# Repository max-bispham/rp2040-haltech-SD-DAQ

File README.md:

# FSAE Backup CAN Logger

**Status:** Hardware architecture selected; firmware and breadboard validation not yet complete.  
**Updated:** October 21, 2026  
**Target:** A practical demonstration for the FSAE electrical-team freshmen on October 22, 2026, at 8 PM.

> **Purpose:** A low-cost, independent backup system that passively captures the car's Haltech CAN traffic onto microSD and presents recorded runs as ordinary files on Windows, macOS, and Linux. This is a data-collection accessory, **not** a replacement for the ECU/PDM, safety systems, or the main DAQ.

## 1. The design in one minute

- **Microcontroller:** Existing Raspberry Pi **Pico / RP2040**; no replacement development board.
- **CAN interface:** **Waveshare Pico-CAN-B** (SKU 23775) with MCP2515, SIT65HVD230DR, 16 MHz crystal, 3.3 V logic. This replaces the user's existing **8 MHz MCP2515/TJA1050** breakout, which cannot be set to compliant 1 Mbit/s CAN timing.
- **Storage:** Existing SPI microSD breakout, on a separate RP2040 SPI peripheral; breakout model/electrical requirements **still need verification**.
- **Computer connection:** Pico's built-in USB device controller running **USB Mass Storage Class (MSC)**, backed by the microSD card. A computer uses its normal file manager: no serial commands, Python, Wi-Fi, or custom host driver for **retrieving** recordings.
- **USB socket:** Use the Pico's existing **Micro-USB socket on the bench**. For the finished carrier PCB, investigate wiring the already-owned **Adafruit #4090 USB-C breakout** to the Pico's underside USB test pads with short matched traces. Do not connect two simultaneous host cables.
- **Controls:** Button; green power-good indicator; dim/bright red recording indicator; yellow USB-presence indicator.
- **Vehicle power:** A **regulated 5 V supply** fed from a suitable, configured and protected PD16 **battery-voltage** output, **not** the PD16 5 V sensor reference. The final converter and source-selection/backfeed protection circuit are not yet fixed.
- **System software:** C++ using Arduino-Pico, a proven microSD library, TinyUSB MSC, and an MCP2515 driver. **No FreeRTOS required for the first milestone.** PC-side Python handles *optional* decoding/graphing after users have already copied data from the USB drive.
- **Mechanical:** Eventual 2-layer KiCad carrier PCB for the existing modules and a 3D-printed enclosure. An editable **Fritzing wiring sketch is a separate upcoming artifact**. This README does not claim that the wiring is physically verified yet.

### What we already have versus what is new

| Part | Source | Notes |
|---|---|---|
| Raspberry Pi Pico/RP2040 board | Already owned | Assumes a **standard 40-pin Pico pinout**; check variant |
| SPI microSD breakout and microSD card | Already owned | Confirm VCC requirements and module labeling |
| Adafruit 4090 USB-C connector breakout | Already owned | Future enclosure connector, not an SD reader |
| Pushbutton and green/red/yellow LEDs | Already owned | Resistors required |
| **Waveshare Pico-CAN-B** | One replacement module | Needed for 1 Mbit/s and direct 3.3 V interfacing |
| 12 V/battery to 5 V buck converter | Planned order | Only necessary for powered operation in the vehicle |
| Typical resistors/capacitors and connectors | Bench stock | See electrical notes |

**Do not purchase another RP2040, a USB-storage shield, an ESP32, a logic-level translator, or a separate CAN transceiver for this design.** The Waveshare module includes both controller and transceiver and is specified for 3.3 V operation.

## 2. User-facing behavior

1. When vehicle power is applied, the device initializes its CAN receiver and SD card.
2. **Red dim solid** means the logger is ready. Press the button to create a new run.
3. **Red bright, blinking once per second** means recording is active. Every received frame is timestamped and stored, including frames whose meaning is not yet known.
4. Press the button again to stop. The red LED goes **off** while buffers are drained and the FAT filesystem is flushed/closed; once complete the red LED returns to dim solid.
5. Connect a computer over USB. Recording stops/is disabled, the microSD is exclusively handed to the USB mass-storage device, and the computer sees a disk (recommended FAT32 volume label `FSAE_LOGGER`). Users can drag files into a folder without special software.
6. Safely eject the disk before unplugging. After USB disconnect, the logger may return to ready mode once the microSD is reinitialized.
7. Optional: a Python analysis script on an engineering laptop picks the most recent run, decodes the known Haltech channels, and generates graphs. **Python must never be required merely to retrieve log files.**

### LED definitions

| LED | Meaning | Recommended implementation |
|---|---|---|
| Green | Regulated supply in acceptable operating range | GPIO output based on a divider/ADC measurement of the 5 V system rail; do not equate an LED connected to power with precision voltage supervision |
| Red dim solid | SD + logging subsystem initialized, ready | RP2040 PWM low duty cycle |
| Red bright blink at 1 Hz | Recording | RP2040 PWM high duty cycle, 1-second blink period |
| Red off | Booting, finalizing, USB MSC or fault | State machine |
| Yellow on | USB host power (VBUS) is present | Pico's onboard USB VBUS-sense path (GPIO24 on a **standard Pico**) drives separate GPIO LED; host enumeration is a different status |

**Fail-safe behavior:** Never indicate 'recording' when the SD card is missing, full, unmounted, or has failed writes. Log faults/counters in a sidecar when possible.

## 3. Electrical interfaces and proposed GPIO map

**These are proposed electrical assignments, not a finished PCB netlist.** Cross-check the actual Pico variant, SD module pin labels, Waveshare board revision, and the physical board stacking clearance before wiring.

### CAN: Waveshare Pico-CAN-B (manufacturer schematic)

The board contains an MCP2515 with a **16 MHz oscillator** and an **SN65HVD230-family 3.3 V CAN transceiver** (Waveshare product description names it SIT65HVD230DR). The schematic connects:

| CAN signal | RP2040 GPIO | Pico physical pin | Function |
|---|---:|---:|---|
| SPI0 MISO (MCP2515 SO) | GP4 | 6 | Controller -> Pico |
| SPI0 CS0 | GP5 | 7 | Chip select |
| SPI0 SCK | GP6 | 9 | Clock |
| SPI0 MOSI (MCP2515 SI) | GP7 | 10 | Pico -> controller |
| MCP2515 INT | GP21 | 27 | Receive/event interrupt (default 0-ohm option) |
| CAN H | Module terminal | — | CAN high |
| CAN L | Module terminal | — | CAN low |
| CAN ground | Module terminal | — | Reference / harness ground, verify terminal orientation |

**Conflict resolved:** The previous draft used **GP5 for a green/red indicator**; that GPIO now belongs to the CAN module. **Do not use GP5 as an LED.** No additional SPI-level converter is needed with this specified Waveshare module.

**Bus configuration:** Classic CAN, 1,000,000 bit/s, standard 11-bit identifiers. Configure the MCP2515 for its **actual 16 MHz oscillator** and **listen-only receive**; the logger must not transmit commands, acknowledgments or error frames onto the running vehicle's bus. Other active nodes supply any needed ACKs. Verify behavior on an isolated test bus before connecting to the car.

**Termination:** The Waveshare board has a selectable **120 Ω** termination. The existing bus should have **two 120 Ω terminations at its physical endpoints**. If the logger is a short additional stub on an already terminated bus, leave the module's termination **off**. Do not casually add a third termination resistor.

**Important receive limitation:** MCP2515 provides only two hardware receive buffers; SD write stalls can therefore cause real CAN losses even with a RAM queue. Count MCP2515 RX overflow and firmware queue overflow separately, make draining CAN a priority, and load-test under representative bus traffic.

### microSD: separate RP2040 SPI1 peripheral

| SD signal (confirm module silkscreen) | RP2040 GPIO | Pico physical pin |
|---|---:|---:|
| DO / MISO | GP12 | 16 |
| CS / SS | GP13 | 17 |
| CLK / SCK | GP14 | 19 |
| DI / MOSI | GP15 | 20 |
| VCC | 3V3(OUT) **only if the module is 3.3 V compatible** | 36 |
| GND | GND | Any suitable GND pin |

**Breakout specification is still unknown.** Some SD breakout boards expect a **5 V input** because they carry an onboard regulator/level shifting; some expect only **3.3 V**. Confirm the actual board before applying power. Native microSD cards are 3.3 V devices. Put **100 nF ceramic + around 10 µF bulk capacitance** near the module supply, subject to what the module already provides. All grounds must share a valid common reference.

### Controls and indicators (nonconflicting GPIOs)

| Function | RP2040 GPIO | Pico physical pin | Connection |
|---|---:|---:|---|
| Record button | GP2 | 4 | Normally-open switch to GND; internal pull-up; debounce in firmware |
| Red recording LED | GP3 | 5 | GPIO -> 330-1k Ω resistor -> LED -> GND; PWM brightness |
| Green power LED | GP8 | 11 | GPIO -> 330-1k Ω resistor -> LED -> GND |
| Yellow USB LED | GP9 | 12 | GPIO -> 330-1k Ω resistor -> LED -> GND |
| Regulated 5 V rail monitor | GP26 / ADC0 | 31 | Through a voltage divider only; **never feed 5 V directly to a GPIO** |
| Native USB VBUS sense | GP24 (internal Pico wiring) | Not header-accessible | Reads presence of USB VBUS on standard Pico |

**Example voltage divider:** 100 kΩ from regulated 5 V rail to GP26, 100 kΩ from GP26 to ground. At a 5.5 V maximum rail, ADC input is about 2.75 V. Select and calibrate a threshold in firmware; green LED only means the monitored rail passes the defined threshold, not that the power supply is automotive-certified. Confirm ADC reading stability in USB-only operation. Keep LED forward current within Pico GPIO constraints; 330-1k Ω series resistance is appropriate for preliminary testing.

### USB mass storage and the eventual USB-C interface

- **Bench:** Use the Pico's own **Micro-USB** receptacle. The RP2040 already has native USB device hardware; no USB bridge module is required.
- **Storage firmware:** Use Adafruit TinyUSB MSC on Arduino-Pico. A supported SD-card MSC example exists, but it must be adapted to the specific SPI bus and to exclusive SD ownership.
- **Carrier PCB concept:** The standard Pico exposes USB **D- on TP2** and **D+ on TP3** underneath the board; **TP1 is USB-adjacent ground**. The Adafruit #4090 exposes USB-C D-/D+/VBUS/GND and incorporates CC resistors. A two-layer carrier can route the short D+/D- pair over continuous ground with appropriate differential geometry; exact impedance is layout-dependent. Accessing Pico underside pads will require a sound manufacturing/contact method; standard headers alone do not connect the test pads.
- **USB-C caveat:** Connecting a separate USB-C socket to TP2/TP3 leaves the Pico's own Micro-USB receptacle electrically on the same USB interface. **Only one cable/host may be used at a time.** Review stubs, ESD protection, power routing and mechanical reliability before fabrication.
- **Power caveat:** The USB VBUS conductor must not be hard-shorted to a powered vehicle 5 V buck output. Plan proper power-source selection/backfeed blocking. This is deliberately not finalized in the breadboard sketch.
- **Filesystem ownership:** Never have MCU FAT writes active while USB MSC is exporting raw SD sectors. On USB insertion, end the run, flush, close, synchronize the writer, and only then make MSC ready. In MSC mode, the internal logger is locked out. Start with read-only MSC if reliable host read-only behavior is acceptable; test on all three operating systems.
- **Volume label:** Set FAT32 volume label to `FSAE_LOGGER` when formatting the card; the USB product string does not itself set the filesystem volume label.

### Vehicle power (still to be finalized)

The PD16 has a dedicated **5 V sensor supply limited to 200 mA total** (PD16 wiring diagram, Connector A pin 12). This is **not** recommended for the logger; its headroom is shared with other sensors. Configurable high-current PD16 outputs provide **switched battery voltage**, not an adjustable regulated 5 V output. **PWM averaging is not a safe substitute for a buck regulator.**

The proposed final route is: appropriately programmed/fused PD16 high-side battery output -> suitable 12 V-to-5 V buck converter -> protected, backfeed-safe 5 V logger supply -> Pico VSYS and any compatible peripherals. Keep USB power availability for file retrieval with the vehicle switched off. Test supply behavior during startup/shutdown and SD writes; an ordinary low-cost buck should not automatically be treated as a fully transient-qualified automotive design.

**For today, use the Pico's normal USB power. No buck converter is required for simulated data/SD/MSC development at the desk.**

## 4. Firmware architecture (proposed; code not started)

```text
Waveshare CAN H/L -> 16 MHz MCP2515/SIT65HVD230 -> SPI0 + GP21 interrupt
                                                    |
                                         Receive + timestamp raw frame
                                                    |
                                               RAM ring buffer
                                                    |
                                       batched, sequential SD writer
                                                    |
                           SPI1 -> microSD FAT32 -> RUN00001.BIN, etc.
                                                    |
                      exclusive ownership handoff (recording stopped)
                                                    |
                     Native RP2040 USB device -> USB MSC -> host file manager
```

Design principles:

1. **Log raw CAN frames first; decode later.** This preserves Elite ECU, PD16, wideband and other traffic even when interpretation is incomplete.
2. Start with a simple nonblocking single-core implementation for generated traffic and SD/USB bring-up. Once hardware CAN is connected, test whether SD stalls cause MCP2515 hardware overrun. If necessary, use RP2040's two cores with a synchronized queue and separate SPI peripherals: one core continuously services CAN; the other writes SD. Two SPI interfaces **alone** do not make CPU operations concurrent.
3. Avoid FreeRTOS for v1. It is an option only if measurable timing/ownership requirements justify it.
4. Allocate fixed-size buffers; prohibit indefinite blocking in the receive path. Record dropped-frame/overflow/write-error counters rather than silently misrepresenting missing data.
5. Have exactly one owner of the SD controller/filesystem at a time: recorder **or** USB host mass storage.
6. USB storage and recording are **mutually exclusive**. USB attachment during recording should stop and finalize first, then enumerate or report unit-not-ready until the card is released.
7. Storage is a **best-effort backup** without a guaranteed power-fail hold-up. Periodically flush and validate how logs behave under unexpected removal of power.

### Logical states

```text
BOOT -> READY -> RECORDING -> FINALIZING -> READY
            \                         /
             \--- USB insertion -----/ -> USB_MSC -> (USB disconnect) -> READY
Any state --(unrecoverable fault)--> ERROR
```

USB MSC must never advertise the card as ready while the MCU still has open log files. A USB cable connected to a USB-powered logger is not the same as a connected host successfully mounting a filesystem: separate those diagnostics when testing.

## 5. Log file format (design proposal; freeze before code generation)

Use FAT32 and incrementing session filenames such as `RUN00001.BIN` plus a human-readable `RUN00001.JSON` summary on a **clean stop**. No real-time clock is assumed; filename/session index, not creation date, defines the latest run.

The format below is a proposal from the first planning draft, retained for continuity. It is **not** a Haltech proprietary format and not yet implemented.

**32-byte header** (all container integers little-endian):

| Offset | Bytes | Field |
|---:|---:|---|
| 0 | 8 | ASCII `FSAECAN1` |
| 8 | 2 | Format version = 1 (`uint16`) |
| 10 | 2 | Header size = 32 (`uint16`) |
| 12 | 2 | Record size = 24 (`uint16`) |
| 14 | 2 | Flags = 0 (`uint16`) |
| 16 | 4 | Timebase ticks per second = 1,000,000 (`uint32`) |
| 20 | 4 | Session number (`uint32`) |
| 24 | 8 | Reserved zeros |

**24-byte frame record** (`struct` format `<QHBB8sI`):

| Offset | Bytes | Field |
|---:|---:|---|
| 0 | 8 | Microseconds since start of run (`uint64`) |
| 8 | 2 | Standard CAN ID (`uint16`, 0–0x7FF) |
| 10 | 1 | DLC (`uint8`, 0–8) |
| 11 | 1 | Flags; zero for ordinary standard CAN data frame |
| 12 | 8 | Raw CAN payload bytes, zero-padded only beyond DLC |
| 20 | 4 | Monotonic sequence number (`uint32`) |

**Important:** Haltech's **payload bytes remain unchanged**. The binary container's little-endian integers and Haltech's big-endian *signal interpretation* are separate concepts. Include a clean-stop JSON with frame counts, queue drops, MCP2515 overflow counts, SD write errors, bitrate/oscillator, session number, and whether finalization succeeded. Be tolerant of truncation or missing JSON after sudden loss of power.

Example bandwidth: 5,000 recorded frames/s × 24 bytes = **120,000 bytes/s** not counting filesystem overhead. Size the RAM queue according to measurement, not that one example alone.

## 6. CAN protocol notes from the attached Haltech PDFs

**ECU Broadcast CAN Protocol v2.0:** 1 Mbit/s; standard 11-bit IDs; big-endian multibyte fields; listed ECU Elite firmware **3.11+** for full support. Available broadcast channels depend on the ECU firmware and actual NSP setup. A CAN logger cannot access arbitrary internal ECU logger channels that are not transmitted on the bus.

| ECU ID | Documented rate | Sample decoding targets |
|---|---:|---|
| `0x360` | 50 Hz | Bytes 0–1 RPM (`u16be`); 2–3 manifold pressure kPa absolute (`u16be / 10`); 4–5 throttle % (`u16be / 10`) |
| `0x361` | 50 Hz | 0–1 fuel pressure kPa gauge (`u16be/10 - 101.3`); 2–3 oil pressure gauge (same) |
| `0x362` | 50 Hz | 0–1 and 2–3 injector duty cycles; 4–5 ignition angle (`s16be/10`) |
| `0x368` | 20 Hz | Four wideband lambda values: consecutive 16-bit unsigned words divided by 1,000 |
| `0x36C` | 20 Hz | Four wheel speeds in km/h: four unsigned 16-bit words divided by 10 |
| `0x372` | 10 Hz | 0–1 battery voltage V (`u16be/10`) |
| `0x3E0` | 5 Hz | Four temperatures: each `u16be/10` Kelvin, then subtract 273.15 for Celsius |

**PD16 Multiplexed CAN Protocol v2.0 (newly supplied PDF):** Also uses 1 Mbit/s, 11-bit IDs, and big-endian values. PD16 base CAN identifiers: **A `0x6D0`, B `0x6D8`, C `0x6E0`, D `0x6E8`**. The first payload byte of a multiplexed message selects IO type/index; **do not** interpret every message sharing a CAN ID as the same channel without using that multiplex field. The document separately defines **PD16-to-ECU** broadcast IDs for monitored input states (PD16 A includes `0x320`, `0x324`, `0x328` at listed 100 Hz rates). Device commands and reported state data are different directions. Read the protocol tables before building a full decoder.

See PDF source files at project root or team repository `docs/` folder, as available:

- `Broadcast_CAN_Protocol_Document_Version_2.pdf` — ECU protocol, pp. 2–7 and subsequent channel tables.
- `Multiplexed_CAN_Protocol_Document_Version_2.pdf` — PD16 support/IDs, pp. 3, 5, 13–17 and later tables.
- `haltech-can-protocol-specification.pdf` — supplementary bit addressing, units and conventions.

The ECU's `0x368` values are **ECU-broadcast wideband channels**; an independent wideband module may use another protocol. Record every ID and determine what really appears on the car before promising channel coverage.

## 7. Desktop analysis expectations

The **USB drive** is the nontechnical user's default interface. Its raw run files must be accessible without Python. A separate, engineering-oriented Python program may:

1. Select the numerically highest valid `RUNxxxxx.BIN`, or accept a specific file path.
2. Validate header, DLCs, record length, monotonic time/sequence, and truncated tail data.
3. Decode known Elite/PD16 channels with proper byte order, signedness, rates and scaling; retain unknown frames.
4. Plot selected channels against **run-relative time** (RPM, throttle, MAP, fuel/oil pressure, coolant temperature, voltage, lambda, PD16 power-channel data where documented/observed).
5. Export selected channels as CSV for Excel or other tools; a double-clickable desktop front end can come later, but is not needed merely to copy logs.

## 8. Recommended development stages

| Milestone | What to demonstrate | Requires new CAN module? |
|---|---|---|
| 1. SD smoke test | Initialize card; write/read a test file | No |
| 2. Simulated run capture | Generate plausible test CAN frames, record on button press and stop reliably | No |
| 3. Native USB mass storage | Mount card in Windows/Linux/macOS file manager via Pico Micro-USB; safely copy files | No |
| 4. Indicators and ownership | LED states; no simultaneous host/MCU card access; repeated start/stop/eject cycles | No |
| 5. PC decoder/plots | Convert simulated log to sensible graphs / CSV | No |
| 6. Receive CAN traffic | Initialize Waveshare MCP2515 at 16 MHz/1 Mbps, listen-only, count overflows | **Yes** |
| 7. Stress test | CAN bursts while SD writes, verify no silent losses | **Yes** |
| 8. Car integration | Check vehicle CAN termination/bus configuration and safely compare data with NSP | **Yes** |
| 9. Carrier and enclosure | Fritzing wiring sketch, KiCad PCB, USB-C routing, final power circuit | Physical measurements and review |

**Meeting goal:** Demonstrate steps 1–5 if time permits, with generated data; clearly label simulated traffic so it is not confused with live car data. A functioning, honestly limited prototype is better than an unverified complete system.

### Draft repository layout

```text
fsae-can-logger/
├── README.md
├── firmware/
│   ├── include/           # config/pin map; logging record definition
│   └── src/               # app, state machine, CAN, SD, USB MSC, LEDs
├── tools/
│   └── plot_latest.py     # engineering-side decoder and plots (planned)
├── tests/
│   └── ...                # fake frames, binary parser tests (planned)
├── hardware/
│   ├── fritzing/          # future editable .fzz sketch
│   └── kicad/             # future carrier board
└── docs/
    └── ...                # optional copies of Haltech PDFs
```

## 9. Outstanding questions (before fabrication, not blockers for milestone 1)

- Exact model/photo of microSD breakout; verify whether its **VCC** is 3.3 V or 5 V, presence of level shifting and on-board capacitors.
- Exact variant of the Pico and access to its pins while Pico-CAN-B is stacked.
- Whether Waveshare module arrives as ordered; verify its crystal and physical jumper position. Confirm **MCP2515 INT on GP21** and controller CS on GP5 on the delivered board.
- Existing CAN physical-end termination, tap length, and Elite CAN broadcast configuration.
- Selected PD16 high-side power pin, programmed fuse/enable behavior, regulated 5 V converter, and USB/vehicle power source-selection protection.
- Mechanical arrangement and tolerances of the Pico, CAN module, SD breakout and USB-C breakout, including Pico underside USB test-pad contact plan.
- Whether the initial USB drive will be **read-only** or writable by the host; in either case enforce exclusive SD ownership.
- Whether USB should stop an ongoing run automatically or require the operator to press Stop first. Default recommendation: automatic safe finalization when feasible, never immediate raw mounting during active recording.

## 10. Updated and spelling-corrected project brief

> I have an opportunity to develop a backup data logger for our FSAE team's car. Our primary data acquisition system may not be fully reliable or ready for testing, so I want an independent system that collects data already transmitted on the car's CAN network. I want a concrete proposal and ideally a small demonstration for our freshmen team members tomorrow at 8 PM.
>
> The car uses a Haltech Elite 1500 ECU, a Haltech Nexus PD16 power distribution module, and a Haltech CAN-connected oxygen sensor. Much of the information we want is already on the CAN bus. The backup device should capture complete raw CAN frames to a microSD card and allow us to decode and graph selected measurements after a run.
>
> The most important usability requirement is that any team member, including mechanical engineers who do not know Python or command-line tools, can plug the device into a Windows, macOS, or Linux laptop and see the recorded files in the operating system's file manager. Wi-Fi is not suitable as the primary retrieval method because the laptop may not be near the car after a run, and connecting the car to the university network is inconvenient.
>
> Hardware requirements: a CAN reader compatible with Haltech's 1 Mbit/s, 11-bit classic CAN network; an SPI microSD card interface; native USB mass storage, eventually through our Adafruit #4090 USB-C connector breakout; a green adequate-power LED; a red status LED that is faint and steady in standby, bright and blinking once per second during recording, and off while processing or not ready; a yellow USB-connected LED; and a pushbutton to start/stop recording. The unit should eventually be powered by a protected, regulated 5 V source from the PD16 system.
>
> We chose our existing RP2040/Pico because it is inexpensive, has native USB device support and enough capacity for a small CAN-to-SD logger. Our current MCP2515/TJA1050 module has an 8 MHz crystal and is not a good match for 1 Mbit/s operation, so we are replacing **only that CAN module** with a Waveshare Pico-CAN-B, which includes a 16 MHz MCP2515 and 3.3 V CAN transceiver. We will reuse our existing microSD breakout, LEDs, pushbutton and USB-C breakout. We do not need FreeRTOS unless later measurements demonstrate a need.
>
> Eventually the components will mount to a two-layer KiCad carrier PCB manufactured at school, inside a 3D-printed enclosure. We may use Fritzing for a clear editable breadboard wiring diagram. The design does not have to be waterproof but must be electrically safe for a passive, receive-only connection to the car and able to produce useful, retrievable logs.
>
> Please help validate the hardware, architecture and pinout; identify specification mismatches; document the system and protocols; plan realistic development phases; and prepare reviewed, modular prompts for Claude to implement the firmware and Python analysis tools. Do not begin generating code until we approve the design and set up the development environment and breadboard.

## 11. Verified reference links

- [Waveshare Pico-CAN-B product page (SKU 23775)](https://www.waveshare.com/product/pico-can-b.htm)
- [Waveshare Pico-CAN-B schematic (Pico pin map, controller/transceiver, 16 MHz clock)](https://files.waveshare.com/upload/1/13/PICO-CAN-B-sch.pdf)
- [Waveshare Pico-CAN-B documentation](https://www.waveshare.com/wiki/Pico-CAN-B)
- [Raspberry Pi Pico datasheet (pinout, USB TP1/TP2/TP3, supply constraints)](https://datasheets.raspberrypi.com/pico/pico-datasheet.pdf)
- [Adafruit USB-C breakout #4090](https://www.adafruit.com/product/4090)
- [Arduino-Pico USB / Adafruit TinyUSB documentation](https://arduino-pico.readthedocs.io/en/latest/usb.html)
- [Adafruit TinyUSB SD-card USB MSC example](https://github.com/adafruit/Adafruit_TinyUSB_Arduino/blob/master/examples/MassStorage/msc_sd/msc_sd.ino)
- [Haltech PD16 wiring diagram (5 V sensor supply: 200 mA maximum)](https://www.jbtechracing.com/wp-content/uploads/2023/10/PD16_WiringDiagram-1.pdf)
- [Haltech Elite/ECU broadcast CAN reference](https://support.haltech.com/portal/en/kb/articles/haltech-can-ecu-broadcast-protocol)
- [Haltech PD16 multiplexed CAN reference](https://support.haltech.com/portal/en/kb/articles/haltech-can-pd-16-protocol)
- [Fritzing application](https://github.com/fritzing/fritzing-app)
- [Fritzing parts library](https://github.com/fritzing/fritzing-parts)
- [Fritzing editable `.fzz` sketch format](https://github.com/fritzing/fritzing-app/wiki/2.2-Sketch-file-format)

---

**Validation status:** This README is a reviewed *design specification*, not a proof of successful bench or vehicle operation. The SPI pin assignment for the Waveshare CAN module is based on its published schematic. The SD breakout, dual-power circuit and USB-C carrier implementation must be confirmed on the actual hardware before making a production PCB or tapping the live car network.

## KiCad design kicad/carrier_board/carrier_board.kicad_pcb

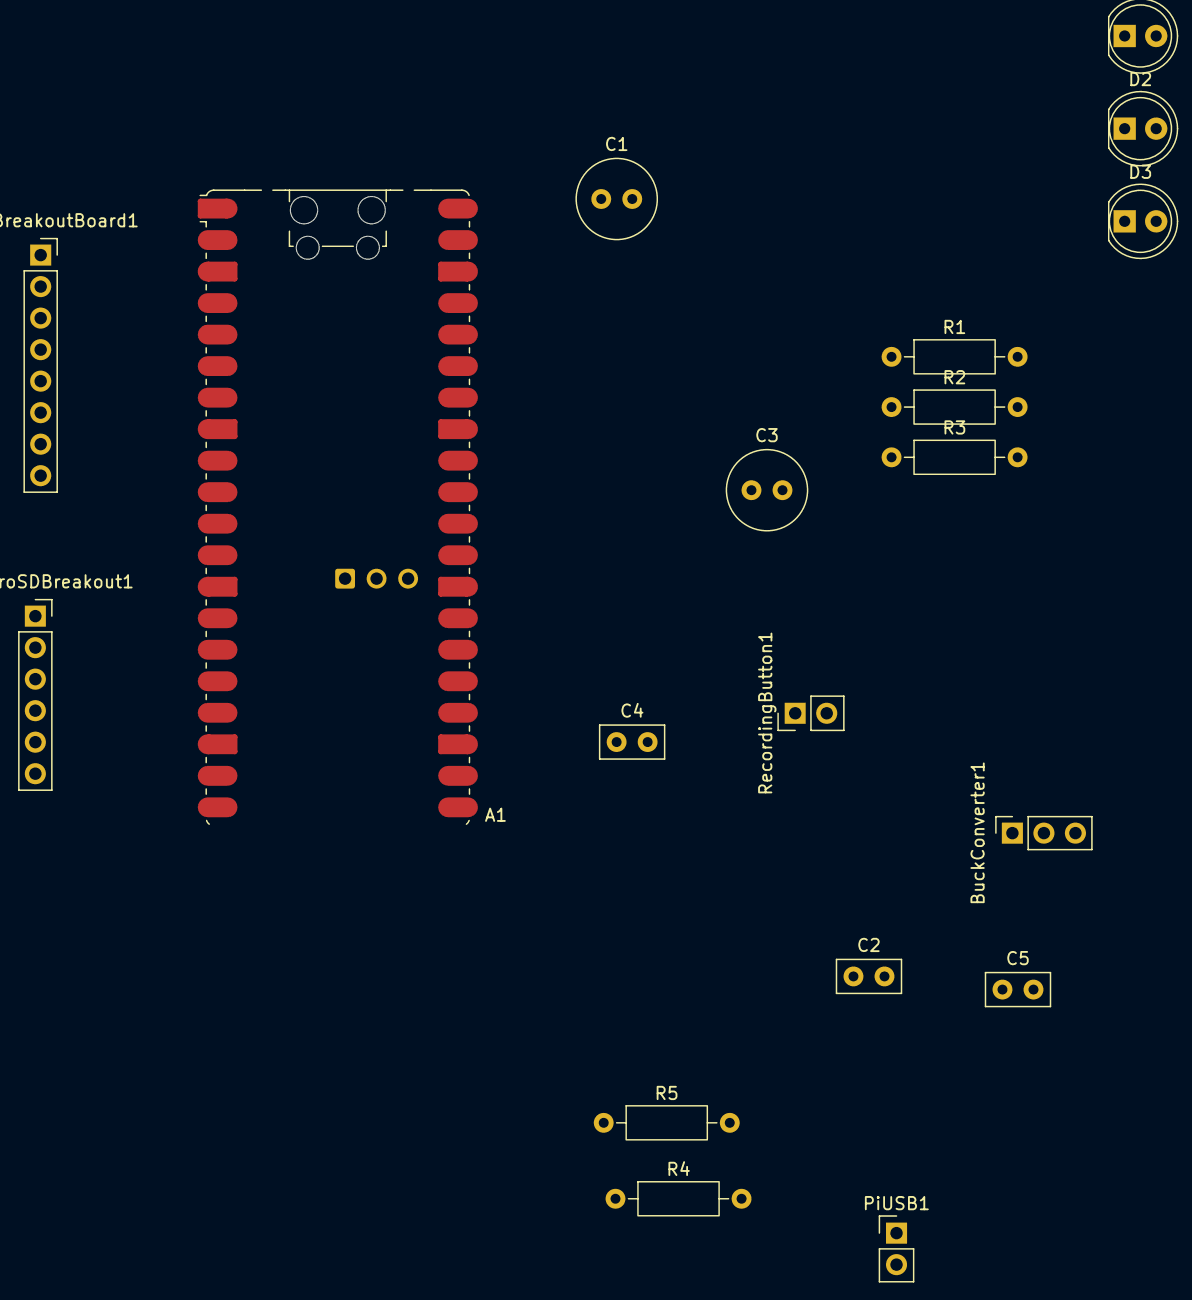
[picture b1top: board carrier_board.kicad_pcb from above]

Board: 2 copper layers, 19 parts (0 on the bottom side), 18 nets, no tracks yet.

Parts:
A1: RaspberryPi_Pico_W; RaspberryPi_Pico_W_SMD_HandSolder
BuckConverter1: Conn_01x02; PinSocket_1x03_P2.54mm_Vertical
C1: 22µf; C_Radial_D6.3mm_H11.0mm_P2.50mm
C2, C4, C5: 100nf; C_Disc_D5.0mm_W2.5mm_P2.50mm
C3: 10µf; C_Radial_D6.3mm_H11.0mm_P2.50mm
D1, D2, D3: LED; LED_D5.0mm
PiUSB1: Conn_01x02; PinHeader_1x02_P2.54mm_Vertical
R1, R2, R3: R; R_Axial_DIN0207_L6.3mm_D2.5mm_P10.16mm_Horizontal
R4: 4k7; R_Axial_DIN0207_L6.3mm_D2.5mm_P10.16mm_Horizontal
R5: 330; R_Axial_DIN0207_L6.3mm_D2.5mm_P10.16mm_Horizontal
RecordingButton1: Conn_01x02; PinHeader_1x02_P2.54mm_Vertical
SPIMicroSDBreakout1: Conn_01x06; PinSocket_1x06_P2.54mm_Vertical
USBCBreakoutBoard1: Conn_01x08; PinSocket_1x08_P2.54mm_Vertical

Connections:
+3.3V: A1.36 (3V3), D1.2 (A), SPIMicroSDBreakout1.6 (3v3)
+3V3: C3.1, C4.1, R4.1
+5V: A1.39 (VSYS), BuckConverter1.1 (+), C1.1, C2.1
/BTN_REC: A1.4 (GPIO2), R5.1
/CS: A1.17 (GPIO13), SPIMicroSDBreakout1.5 (CS)
/D+: PiUSB1.1 (D+), USBCBreakoutBoard1.3 (D+)
/D-: PiUSB1.2 (D-), USBCBreakoutBoard1.4 (D-)
/LED_REC: A1.5 (GPIO3), D2.2 (A)
/LED_USB: A1.11 (GPIO8), D3.2 (A)
/MISO: A1.16 (GPIO12), SPIMicroSDBreakout1.2 (MISO)
/MOSI: A1.15 (GPIO11), SPIMicroSDBreakout1.4 (MOSI)
/SCK: A1.14 (GPIO10), SPIMicroSDBreakout1.3 (CLK)
/USB5v: A1.40 (VBUS), USBCBreakoutBoard1.7 (VBUS)
GND: A1.3 (GND), A1.8 (GND), A1.13 (GND), A1.18 (GND), A1.23 (GND), A1.28 (GND), A1.33 (AGND), A1.38 (GND), BuckConverter1.2 (-), C1.2, C2.2, C3.2, C4.2, C5.2, R1.1, R2.1, R3.1, RecordingButton1.2, SPIMicroSDBreakout1.1 (GND), USBCBreakoutBoard1.8 (GND)
unnamed: D1.1 (K), R1.2
unnamed: D2.1 (K), R2.2
unnamed: D3.1 (K), R3.2
unnamed: C5.1, R4.2, R5.2, RecordingButton1.1
